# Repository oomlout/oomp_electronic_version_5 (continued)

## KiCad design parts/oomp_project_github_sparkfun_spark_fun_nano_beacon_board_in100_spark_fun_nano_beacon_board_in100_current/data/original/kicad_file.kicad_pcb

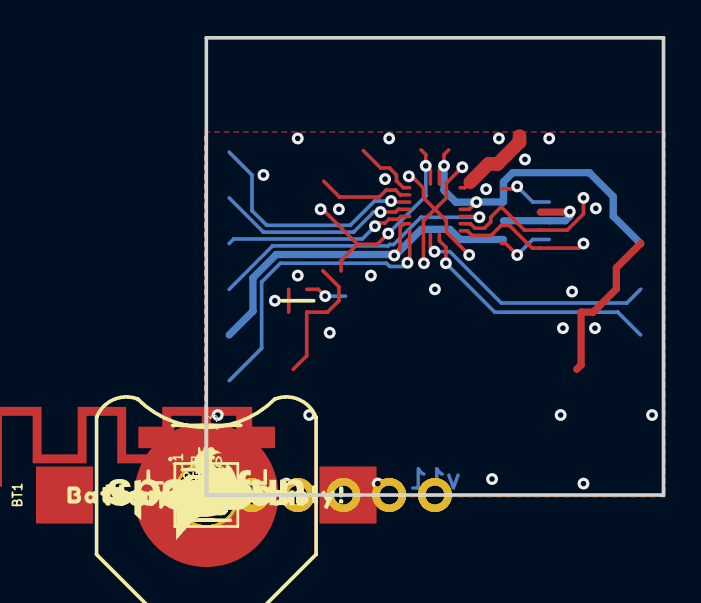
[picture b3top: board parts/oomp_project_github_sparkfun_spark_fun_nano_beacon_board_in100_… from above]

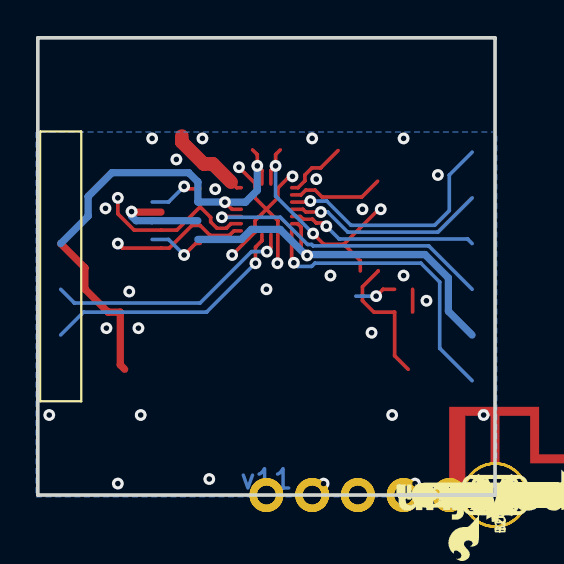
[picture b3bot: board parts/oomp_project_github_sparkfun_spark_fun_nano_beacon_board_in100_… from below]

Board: 2 copper layers, 25.4 x 25.4 mm, 63 parts (24 on the bottom side), 21 nets.

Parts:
BT1: BATTCON_12MM
BUS0: JUMPER-SMT_3_1-NC_TRACE_SILK; SMT-JUMPER_3_1-NC_TRACE_SILK
C1, C3: 0.1uF; 0402-TIGHT
C2: 10uF; 0402-TIGHT
D1: DNP; LED-0402
DEV0: PROD_ID_PASTE_SILK; PRODUCT_IDENT_PASTE_SILK
E1: ANTENNA-GROUNDEDTRACE-15.2MM-MIRROR; TRACE_ANTENNA_2.4GHZ_15.2MM_MIRROR
FD1, FD2, FD3, FD4: FIDUCIAL1X2; FIDUCIAL-1X2
FRAME1: FRAME-LETTER; CREATIVE_COMMONS
H1, H2: STAND-OFF
I2C0: JUMPER-SMT_3_2-NC_TRACE_SILK; SMT-JUMPER_3_2-NC_TRACE_SILK
J1, J2: 1X06_NO_SILK
J3: Vertical Qwiic Connector; JST04_1MM_VERT
LOGO1: OSHW-LOGOS; OSHW-LOGO-S
LOGO2: SFE_LOGO_NAME_FLAME.1_INCH; SFE_LOGO_NAME_FLAME_.1
LOGO3: QWIIC_LOGO_5MM; QWIIC_5MM
PRO0: PROD_ID_PASTE_SILK; PRODUCT_IDENT_PASTE_SILK
PWR0: JUMPER-SMT_2_NC_TRACE_SILK; SMT-JUMPER_2_NC_TRACE_SILK
R1: DNP; 0402-TIGHT
R2: 1k; 0402-TIGHT
R3, R4: 2.2k; 0402-TIGHT
RST0: DNP; TACTILE_SWITCH_SMD_4.6X2.8MM
TP1, TP2, TP3: TEST-POINT3; PAD.03X.03
U1: IN100
U$1, U$29: NANOBEACON0
U$2: #_7#0
U$3: #_6#0
U$4: SFE_LOGO_NAME_.1
U$5, U$31: IN1000
U$6: #_5#0
U$7: #_4#0
U$8: SFE_LOGO_FLAME_.2
U$9: BATTERY_OR_VCC_ONLY##0
U$11: #I2C#0
U$12: #NOTES#0
U$13: #IO7_#0
U$14: #IO6_#0
U$15: #IO5_#0
U$16: #IO4_#0
U$17: #SW0_#0
U$18: #SW1_#0
U$19: #PWR#0
U$20: #SW0#3
U$21: SW00
U$22: SW10
U$23: RST0
U$24: #VCC#0
U$25: #BUS#0
U$26: PWR0
U$28: DEV0
U$30: PRO0
Y1: CRYSTAL-26MHZSMD-3.2X2.5; CRYSTAL-SMD-3.2X2.5MM

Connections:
EN: C3.1, R2.2, RST0.1, RST0.2, TP3.1, U1.18
GND: BT1.GND, C1.2, C2.2, C3.2, E1.GND, J1.6, J3.1, PWR0.1, RST0.3, RST0.4, U1.19, Y1.2, Y1.4
IO4: J2.4, U1.12
IO5: J2.3, U1.5
IO6: J2.2, U1.4
IO7: J2.1, U1.3
unnamed: U1.1, Y1.3
unnamed: U1.2, Y1.1
unnamed: PWR0.2, R1.1
unnamed: E1.ANT, U1.16
unnamed: D1.C, R1.2
unnamed: I2C0.1, R4.2
unnamed: BUS0.2, I2C0.2, J3.2
unnamed: I2C0.3, R3.2
RX/IO0: J1.3, U1.8
SCL/IO2: J3.4, R3.1, TP2.1, U1.10
SDA/IO3: J3.3, R4.1, TP1.1, U1.11
SW0: BUS0.3, J2.5, U1.6
SW1: J2.6, U1.7
TX/IO1: J1.2, U1.9
VCC: BT1.PWR@1, BT1.PWR@2, BUS0.1, C1.1, C2.1, D1.A, J1.4, R2.1, U1.13, U1.17

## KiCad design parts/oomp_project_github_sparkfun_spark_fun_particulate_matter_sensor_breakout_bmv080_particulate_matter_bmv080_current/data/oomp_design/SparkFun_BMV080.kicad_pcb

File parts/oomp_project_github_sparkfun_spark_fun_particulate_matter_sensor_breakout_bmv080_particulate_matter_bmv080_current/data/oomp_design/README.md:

# OOMP KiCad design copy

Open `SparkFun_BMV080.kicad_pro` (or the `.kicad_pcb` / `.kicad_sch`) in KiCad. Local OOMP libraries are under `libraries/`. Original inputs are preserved in [../original/](../original/).

Only verified unchanged installed KiCad defaults were renamed. Modified, custom, unmatched and unavailable items remain unchanged. Soldering variants are never swapped during conversion. Existing pad coordinates, nets and UUIDs are preserved.

See [conversion_report.yaml](conversion_report.yaml) for every conversion and skip. Copy this directory before editing; regeneration refuses to overwrite edited design files.

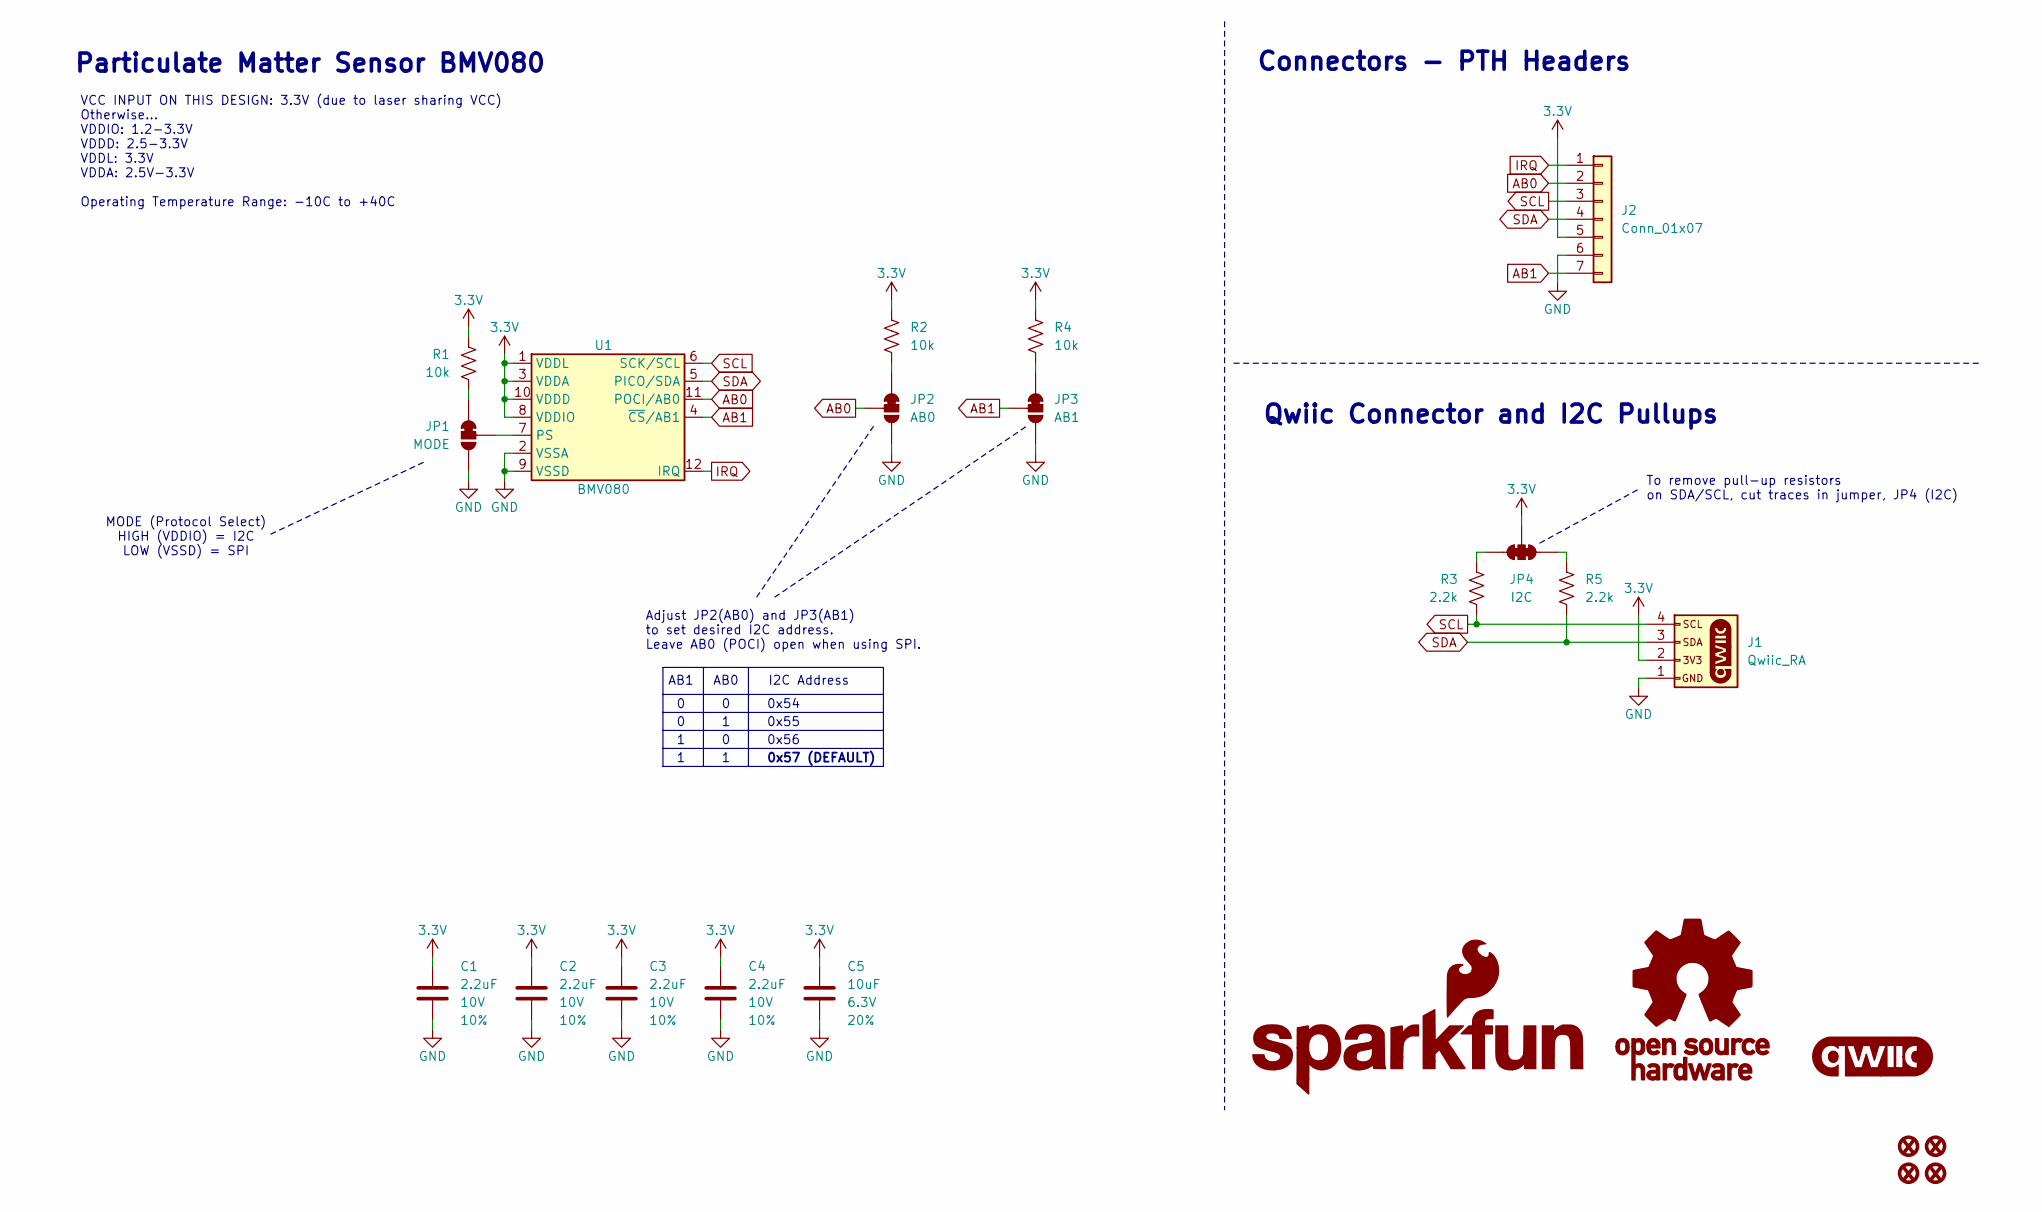
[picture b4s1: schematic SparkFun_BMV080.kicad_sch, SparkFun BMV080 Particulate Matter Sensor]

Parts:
C1, C2, C3, C4: 2.2uF; C_0402_1005Metric; Voltage 10V; Tolerance 10%
C5: 10uF; C_0603_1608Metric; Voltage 6.3V; Tolerance 20%
FID1, FID2, FID3, FID4: Fiducial_0.5mm; Fiducial_0.5mm_Mask1mm
G1: OSHW_Logo; Creative_Commons_License
G2: SparkFun_Logo
G3: qwiic_Logo
J1: Qwiic_RA; JST_SMD_1.0mm-4_RA
J2: Conn_01x07; 1x07
JP1: MODE; Jumper_3_NC-1_Trace_NoSilk
JP2: AB0; Jumper_3_NC-1_Trace_NoSilk
JP3: AB1; Jumper_3_NC-1_Trace_NoSilk
JP4: I2C; Jumper_3_NC-2_Trace_NoSilk
R1, R2, R4: 10k; R_0402_1005Metric
R3, R5: 2.2k; R_0402_1005Metric
U1: BMV080; FPC_0.3mm-13

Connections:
3.3V: C1.1, C2.1, C3.1, C4.1, C5.1, J1.2, J2.5, JP4.2 (C), R1.1, R2.1, R4.1, U1.1 (VDDL), U1.3 (VDDA), U1.8 (VDDIO), U1.10 (VDDD)
AB0: J2.2, JP2.2 (C), U1.11 (POCI/AB0)
AB1: J2.7, JP3.2 (C), U1.4 (~CS/AB1)
GND: C1.2, C2.2, C3.2, C4.2, C5.2, J1.1, J2.6, JP1.3 (B), JP2.3 (B), JP3.3 (B), U1.2 (VSSA), U1.9 (VSSD)
IRQ: J2.1, U1.12 (IRQ)
unnamed: JP1.1 (A), R1.2
unnamed: JP1.2 (C), U1.7 (PS)
unnamed: JP2.1 (A), R2.2
unnamed: JP3.1 (A), R4.2
unnamed: JP4.1 (A), R5.2
unnamed: JP4.3 (B), R3.2
SCL: J1.4, J2.3, R3.1, U1.6 (SCK/SCL)
SDA: J1.3, J2.4, R5.1, U1.5 (PICO/SDA)

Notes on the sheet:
0x54
MODE (Protocol Select) HIGH (VDDIO) = I2C LOW (VSSD) = SPI
AB1
Connectors - PTH Headers
0x57 (DEFAULT)
VCC INPUT ON THIS DESIGN: 3.3V (due to laser sharing VCC) Otherwise... VDDIO: 1.2-3.3V VDDD: 2.5-3.3V VDDL: 3.3V VDDA: 2.5V-3.3V Operating Temperature Range: -10C to +40C
Particulate Matter Sensor BMV080
AB0
0x56
I2C Address
Adjust JP2(AB0) and JP3(AB1) to set desired I2C address. Leave AB0 (POCI) open when using SPI.
0x55
To remove pull-up resistors on SDA/SCL, cut traces in jumper, JP4 (I2C)
Qwiic Connector and I2C Pullups

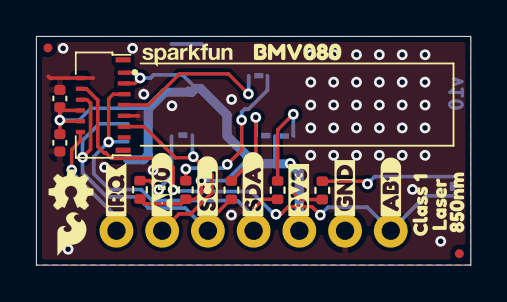
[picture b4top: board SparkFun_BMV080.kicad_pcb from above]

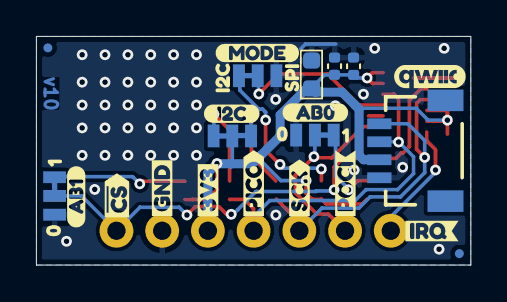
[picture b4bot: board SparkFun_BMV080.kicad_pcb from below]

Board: 2 copper layers, 24.1 x 12.7 mm, 51 parts (27 on the bottom side), 13 nets.

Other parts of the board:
Ref**: Val**; OSHW_Logo_2.5mm
kibuzzard-66BFB450: G***; kibuzzard-66BFB450
kibuzzard-66BFBF9D, kibuzzard-66BFBF9D#2: G***; kibuzzard-66BFBF9D
kibuzzard-66BFBF23: G***; kibuzzard-66BFBF23
kibuzzard-66BFBF70, kibuzzard-66BFBF70#2: G***; kibuzzard-66BFBF70
kibuzzard-66BFC0D2: G***; kibuzzard-66BFC0D2
kibuzzard-66BFC2FE: G***; kibuzzard-66BFC2FE
kibuzzard-66BFC09F: G***; kibuzzard-66BFC09F
kibuzzard-66BFC045: G***; kibuzzard-66BFC045
kibuzzard-66BFC108: G***; kibuzzard-66BFC108
kibuzzard-66BFC288: G***; kibuzzard-66BFC288
kibuzzard-66C3B2A1: G***; kibuzzard-66C3B2A1
kibuzzard-66C3B2DA: G***; kibuzzard-66C3B2DA
kibuzzard-66C3B2FA, kibuzzard-66C3B2FA#2: G***; kibuzzard-66C3B2FA
kibuzzard-66C3B3B1: G***; kibuzzard-66C3B3B1
kibuzzard-66C3B3D3: G***; kibuzzard-66C3B3D3
kibuzzard-66C3B30A, kibuzzard-66C3B30A#2: G***; kibuzzard-66C3B30A
kibuzzard-66C3B31E: G***; kibuzzard-66C3B31E
kibuzzard-66C3B369: G***; kibuzzard-66C3B369
kibuzzard-66C4B81D: G***; kibuzzard-66C4B81D
kibuzzard-66C7A36E: G***; kibuzzard-66C7A36E
kibuzzard-66C77290: G***; kibuzzard-66C77290
kibuzzard-67250BE2: G***; kibuzzard-67250BE2
kibuzzard-67250CD2: G***; kibuzzard-67250CD2
kibuzzard-67250CEE: G***; kibuzzard-67250CEE

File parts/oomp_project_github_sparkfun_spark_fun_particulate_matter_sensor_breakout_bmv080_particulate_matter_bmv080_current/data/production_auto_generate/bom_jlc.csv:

Comment,Designator,Footprint,LCSC Part #
10k,"R1,R2,R4",SparkFun-Resistor:R_0402_1005Metric,C2906861
10uF,C5,SparkFun-Capacitor:C_0603_1608Metric,C19702
2.2k,"R3,R5",SparkFun-Resistor:R_0402_1005Metric,C2906920
2.2uF,"C1,C2,C3,C4",SparkFun-Capacitor:C_0402_1005Metric,C12530
AB0,JP2,SparkFun-Jumper:Jumper_3_NC-1_Trace_NoSilk,
AB1,JP3,SparkFun-Jumper:Jumper_3_NC-1_Trace_NoSilk,
BMV080,U1,SparkFun-Connector:FPC_0.3mm-13,
BMV080_Outline,REF**,SparkFun-Sensor:BMV080_Outline,
Conn_01x07,J2,SparkFun-Connector:1x07,C7501585
I2C,JP4,SparkFun-Jumper:Jumper_3_NC-2_Trace_NoSilk,
MODE,JP1,SparkFun-Jumper:Jumper_3_NC-1_Trace_NoSilk,
Qwiic_RA,J1,SparkFun-Connector:JST_SMD_1.0mm-4_RA,C160404

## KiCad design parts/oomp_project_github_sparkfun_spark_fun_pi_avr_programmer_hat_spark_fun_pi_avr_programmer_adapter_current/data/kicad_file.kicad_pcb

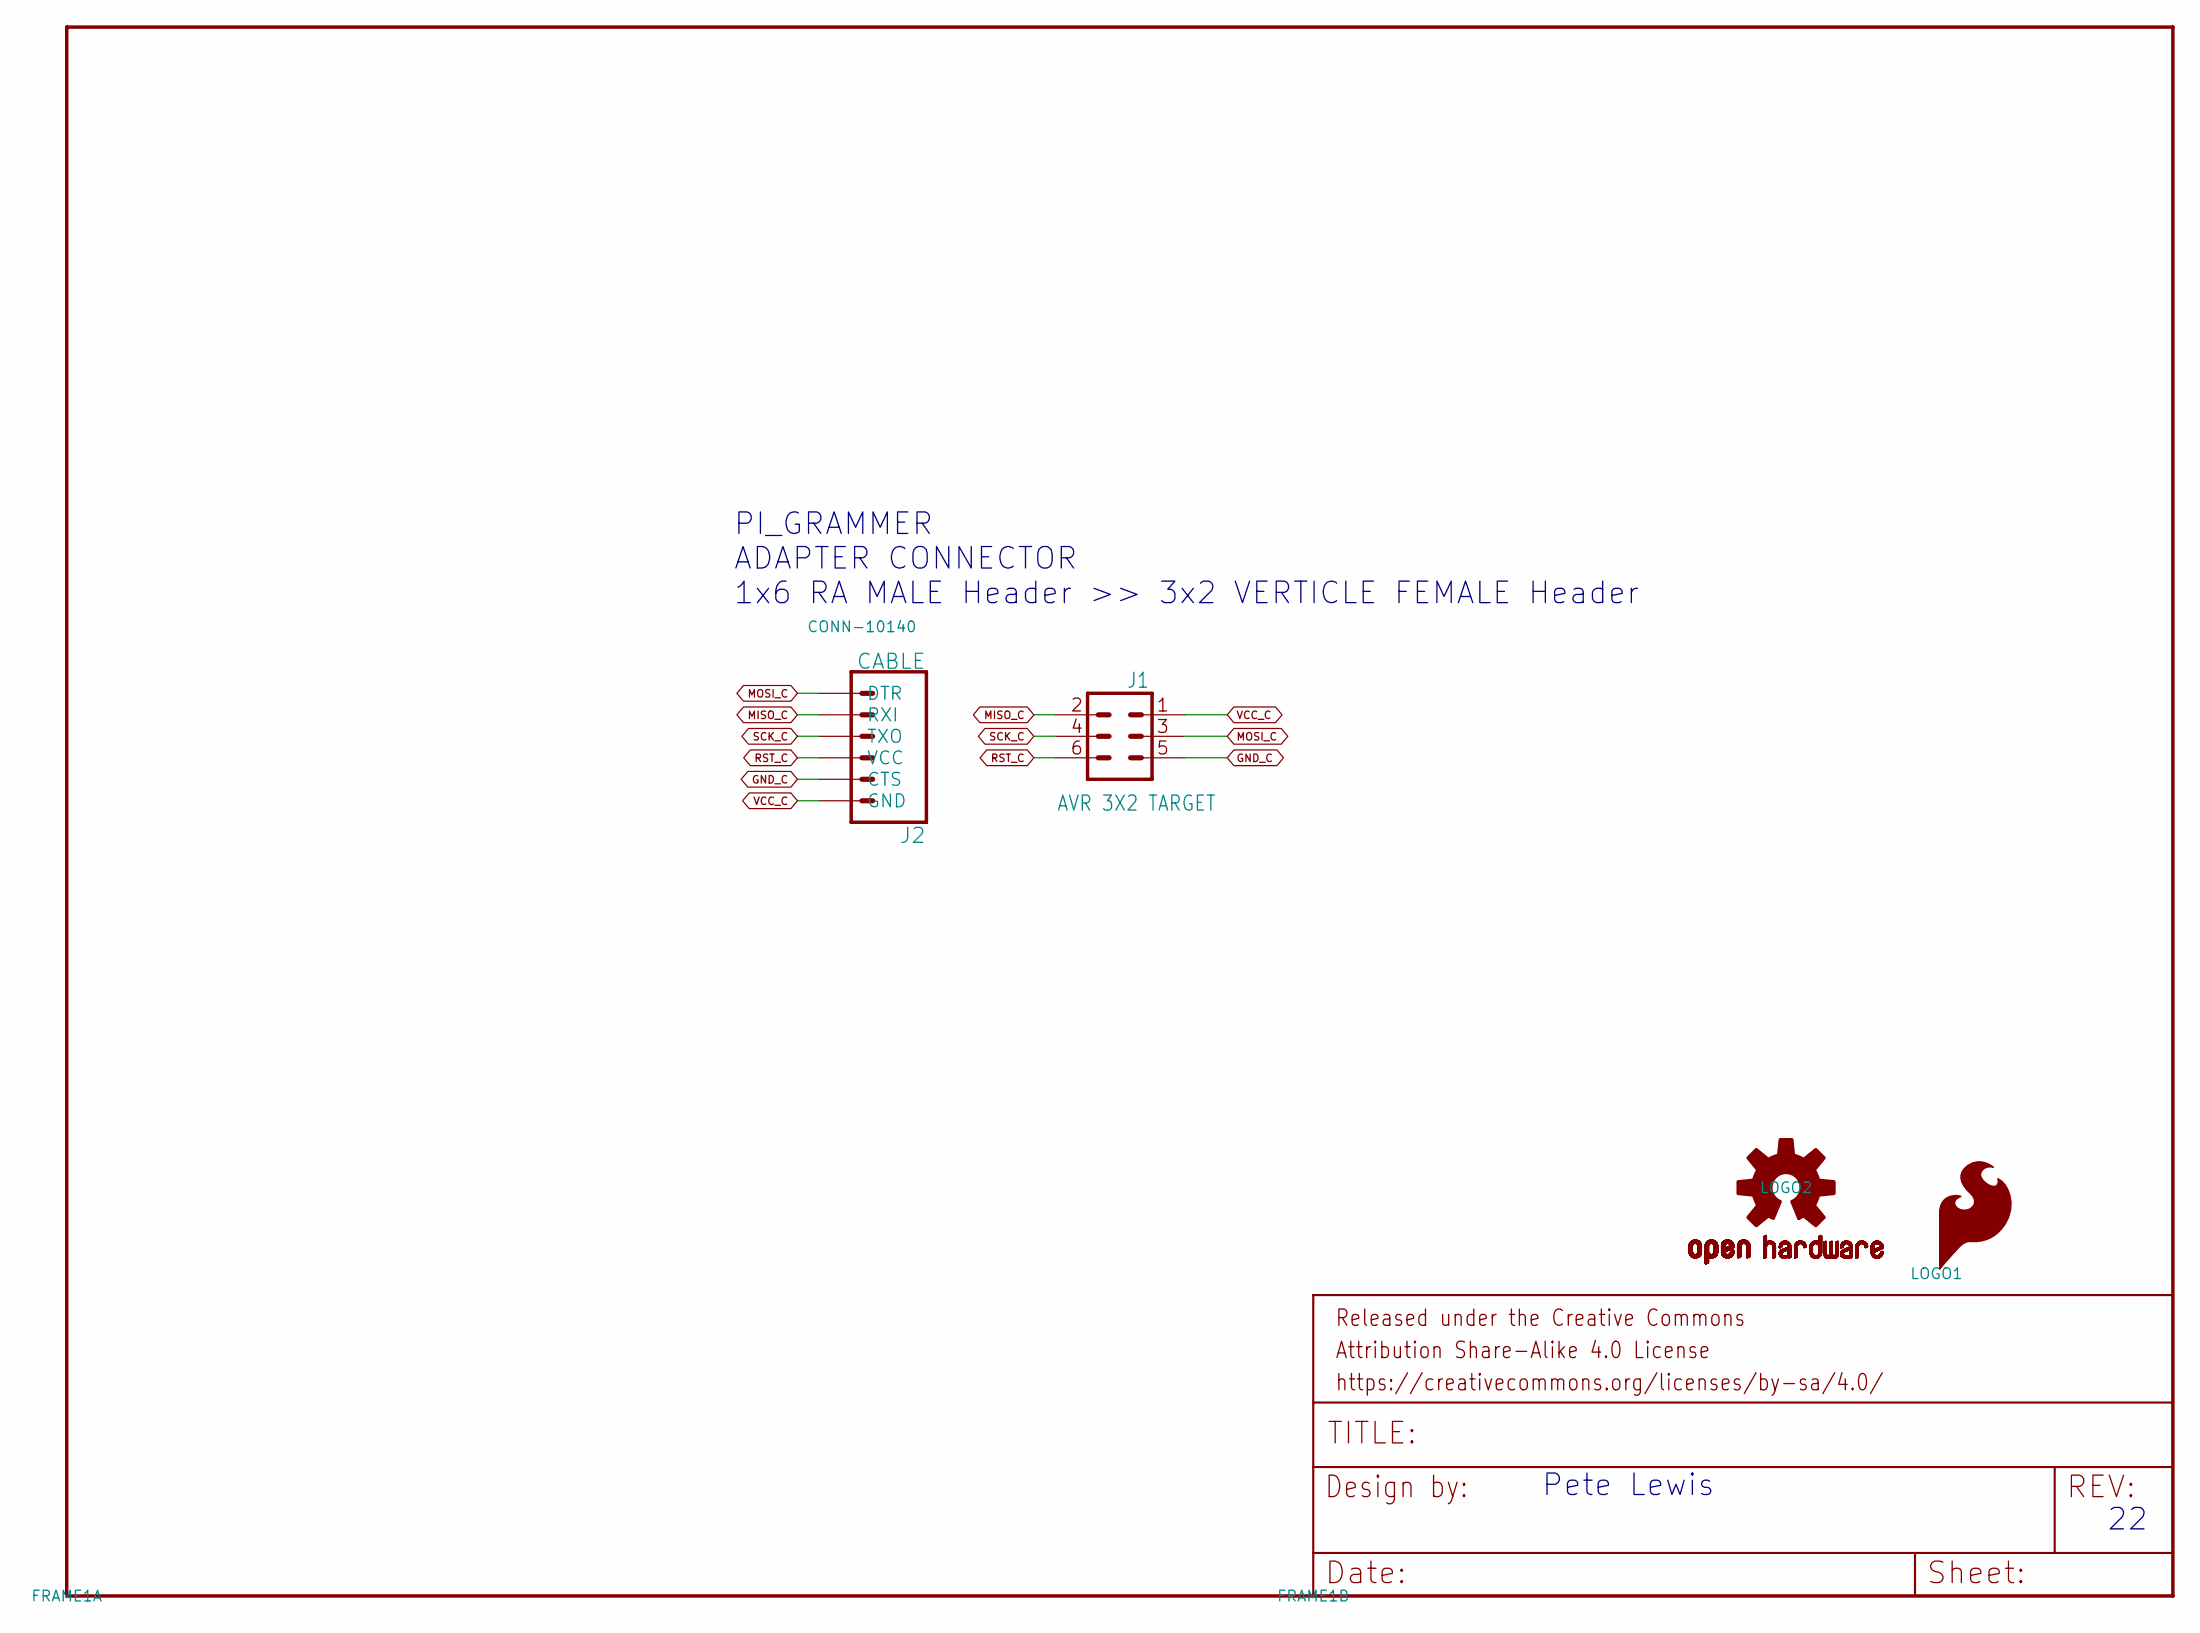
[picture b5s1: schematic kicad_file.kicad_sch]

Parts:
FRAME1: FRAME-LETTER; CREATIVE_COMMONS
J1: AVR 3X2 TARGET; 2X3_SMT_POSTS
J2: CABLE; 1X06-SMD_RA_MALE
LOGO1: SFE_LOGO_FLAME.1_INCH; SFE_LOGO_FLAME_.1
LOGO2: OSHW-LOGOMINI; OSHW-LOGO-MINI

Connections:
GND_C: J1.5, J2.5 (CTS)
MISO_C: J1.2, J2.2 (RXI)
MOSI_C: J1.3, J2.1 (DTR)
RST_C: J1.6, J2.4 (VCC)
SCK_C: J1.4, J2.3 (TXO)
VCC_C: J1.1, J2.6 (GND)

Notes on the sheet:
Pete Lewis
PI_GRAMMER ADAPTER CONNECTOR 1x6 RA MALE Header >> 3x2 VERTICLE FEMALE Header

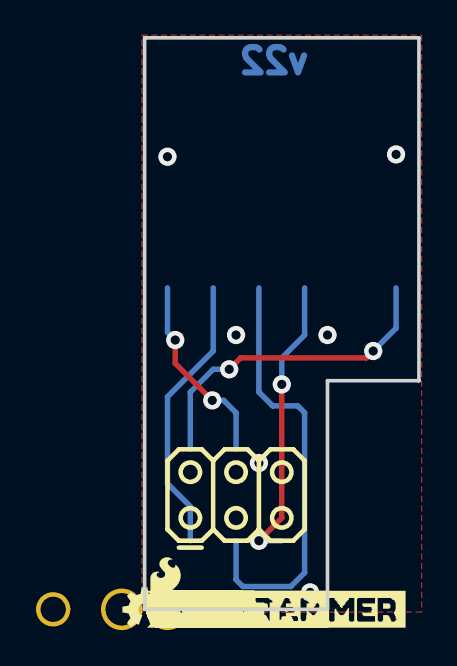
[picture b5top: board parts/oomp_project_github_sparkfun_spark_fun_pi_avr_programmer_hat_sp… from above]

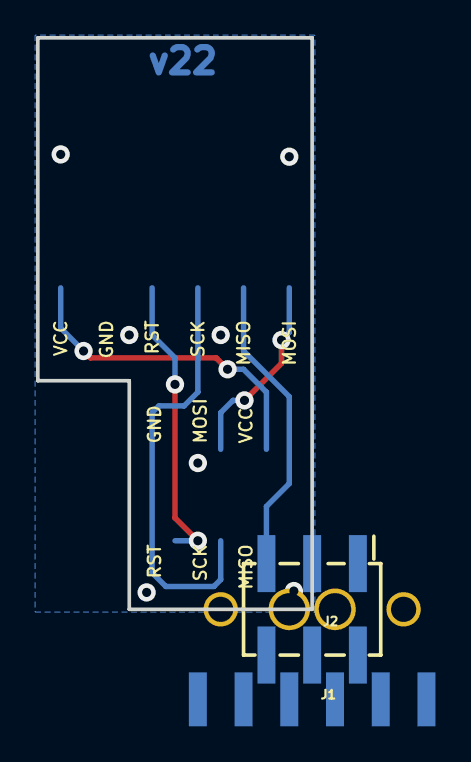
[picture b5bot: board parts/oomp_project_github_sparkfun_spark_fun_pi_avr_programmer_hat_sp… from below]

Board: 2 copper layers, 15.2 x 31.8 mm, 16 parts (2 on the bottom side), 6 nets.

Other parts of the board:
U$1: GND1
U$2: MISO5
U$3: MOSI4
U$4: RST2
U$5: SCK3
U$6: VCC0
U$7: PI0
U$8: AVR1
U$9: PROGRAMMER2
U$10: HAT3
U$11: ADAPTER4

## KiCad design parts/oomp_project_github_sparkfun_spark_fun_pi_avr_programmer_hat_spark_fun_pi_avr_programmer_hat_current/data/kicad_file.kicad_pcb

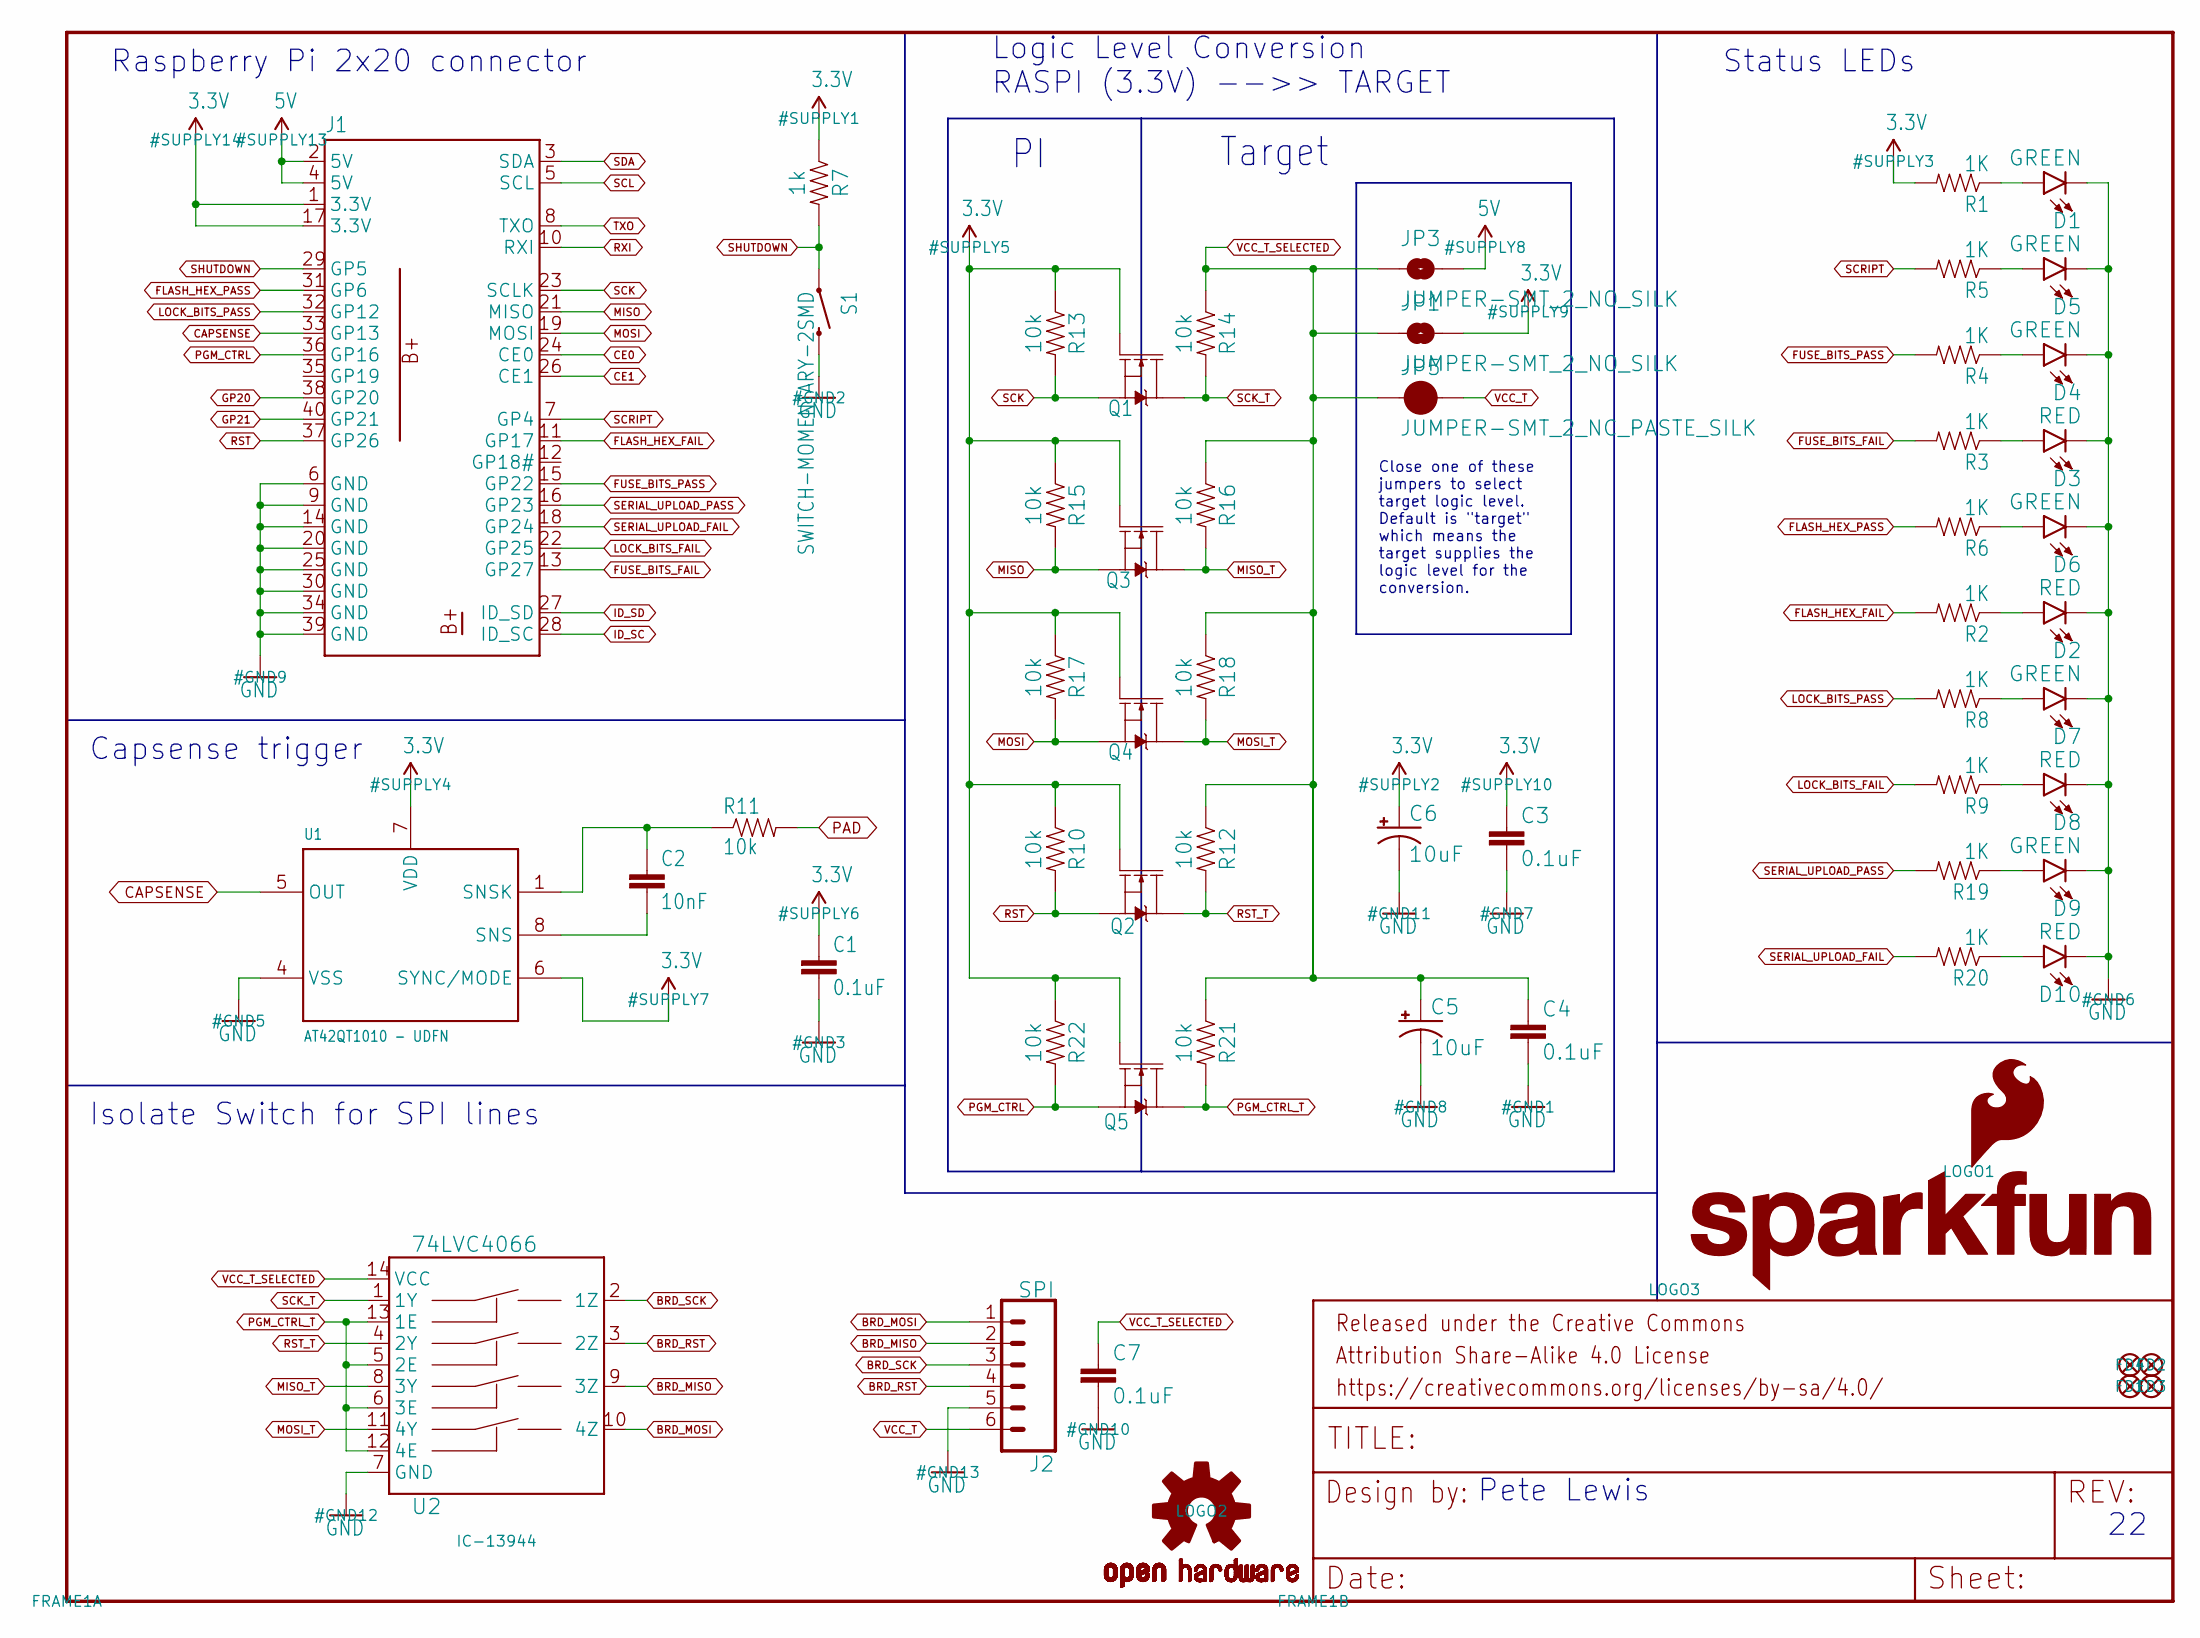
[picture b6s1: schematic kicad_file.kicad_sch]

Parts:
C1: 0.1uF; 0603-CAP
C2: 10nF; 0603-CAP
C3, C4, C7: 0.1uF; 0603
C5, C6: 10uF; EIA3216
D1, D4, D5, D6, D7, D9: GREEN; LED-1206
D2, D3, D8, D10: RED; LED-1206
FD1, FD2, FD3, FD4: FIDUCIALUFIDUCIAL; FIDUCIAL-MICRO
FRAME1: FRAME-LETTER; CREATIVE_COMMONS
J1: RASPBERRYPI-B+-GPIO; 2X20-SHROUDED
J2: SPI; 1X06-SMD_RA_MALE
JP1, JP3: JUMPER-SMT_2_NO_SILK; SMT-JUMPER_2_NO_SILK
JP5: JUMPER-SMT_2_NC_PASTE_SILK; SMT-JUMPER_2_NC_PASTE_SILK
LOGO1: SFE_LOGO_FLAME.2_INCH; SFE_LOGO_FLAME_.2
LOGO2: OSHW-LOGOL; OSHW-LOGO-L
LOGO3: SFE_LOGO_NAME.6_INCH; SFE_LOGO_NAME_.6
Q1, Q2, Q3, Q4, Q5: 220mA/50V/3.5Ω; SOT23-3
R1, R2, R3, R4, R5, R6, R8, R9, R19, R20: 1K; 0603-RES
R7: 1k; 0603
R10, R12, R13, R14, R15, R16, R17, R18, R21, R22: 10k; 0603
R11: 10k; 0603-RES
S1: SWITCH-MOMENTARY-2SMD; TACTILE-SWITCH-SMD
U1: AT42QT1010 - UDFN; UDFN_USON_8_PAD
U2: 74LVC4066; SO14

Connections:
3.3V: C1.1, C3.1, C6.+, J1.1 (3.3V), J1.17 (3.3V), JP1.2, Q1.1 (G), Q2.1 (G), Q3.1 (G), Q4.1 (G), Q5.1 (G), R1.2, R7.1, R10.1, R13.1, R15.1, R17.1, R22.1, U1.6 (SYNC/MODE), U1.7 (VDD)
5V: J1.2 (5V), J1.4 (5V), JP3.2
BRD_MISO: J2.2, U2.9 (3Z)
BRD_MOSI: J2.1, U2.10 (4Z)
BRD_RST: J2.4, U2.3 (2Z)
BRD_SCK: J2.3, U2.2 (1Z)
CAPSENSE: J1.33 (GP13), U1.5 (OUT)
CE0: J1.24 (CE0)
CE1: J1.26 (CE1)
FLASH_HEX_FAIL: J1.11 (GP17), R2.2
FLASH_HEX_PASS: J1.31 (GP6), R6.2
FUSE_BITS_FAIL: J1.13 (GP27), R3.2
FUSE_BITS_PASS: J1.15 (GP22), R4.2
GND: C1.2, C3.2, C4.2, C5.-, C6.-, C7.2, D1.C, D2.C, D3.C, D4.C, D5.C, D6.C, D7.C, D8.C, D9.C, D10.C, J1.6 (GND), J1.9 (GND), J1.14 (GND), J1.20 (GND), J1.25 (GND), J1.30 (GND), J1.34 (GND), J1.39 (GND), J2.5, S1.3 (2), U1.4 (VSS), U2.7 (GND)
GP20: J1.38 (GP20)
GP21: J1.40 (GP21)
ID_SC: J1.28 (ID_SC)
ID_SD: J1.27 (ID_SD)
LOCK_BITS_FAIL: J1.22 (GP25), R9.2
LOCK_BITS_PASS: J1.32 (GP12), R8.2
MISO: J1.21 (MISO), Q3.2 (S), R15.2
MISO_T: Q3.3 (D), R16.2, U2.8 (3Y)
MOSI: J1.19 (MOSI), Q4.2 (S), R17.2
MOSI_T: Q4.3 (D), R18.2, U2.11 (4Y)
unnamed: D6.A, R6.1
unnamed: D1.A, R1.1
unnamed: D2.A, R2.1
unnamed: D3.A, R3.1
unnamed: D7.A, R8.1
unnamed: D4.A, R4.1
unnamed: D5.A, R5.1
unnamed: D8.A, R9.1
unnamed: C2.2, U1.8 (SNS)
unnamed: C2.1, R11.1, U1.1 (SNSK)
unnamed: D9.A, R19.1
unnamed: D10.A, R20.1
PAD: R11.2
PGM_CTRL: J1.36 (GP16), Q5.2 (S), R22.2
PGM_CTRL_T: Q5.3 (D), R21.2, U2.5 (2E), U2.6 (3E), U2.12 (4E), U2.13 (1E)
RST: J1.37 (GP26), Q2.2 (S), R10.2
RST_T: Q2.3 (D), R12.2, U2.4 (2Y)
RXI: J1.10 (RXI)
SCK: J1.23 (SCLK), Q1.2 (S), R13.2
SCK_T: Q1.3 (D), R14.2, U2.1 (1Y)
SCL: J1.5 (SCL)
SCRIPT: J1.7 (GP4), R5.2
SDA: J1.3 (SDA)
SERIAL_UPLOAD_FAIL: J1.18 (GP24), R20.2
SERIAL_UPLOAD_PASS: J1.16 (GP23), R19.2
SHUTDOWN: J1.29 (GP5), R7.2, S1.1
TXO: J1.8 (TXO)
VCC_T: J2.6, JP5.2
VCC_T_SELECTED: C4.1, C5.+, C7.1, JP1.1, JP3.1, JP5.1, R12.1, R14.1, R16.1, R18.1, R21.1, U2.14 (VCC)

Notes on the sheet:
Logic Level Conversion RASPI (3.3V) -->> TARGET
Status LEDs
Capsense trigger
Target
Isolate Switch for SPI lines
Raspberry Pi 2x20 connector
Close one of these jumpers to select target logic level. Default is "target" which means the target supplies the logic level for the conversion.
Pete Lewis

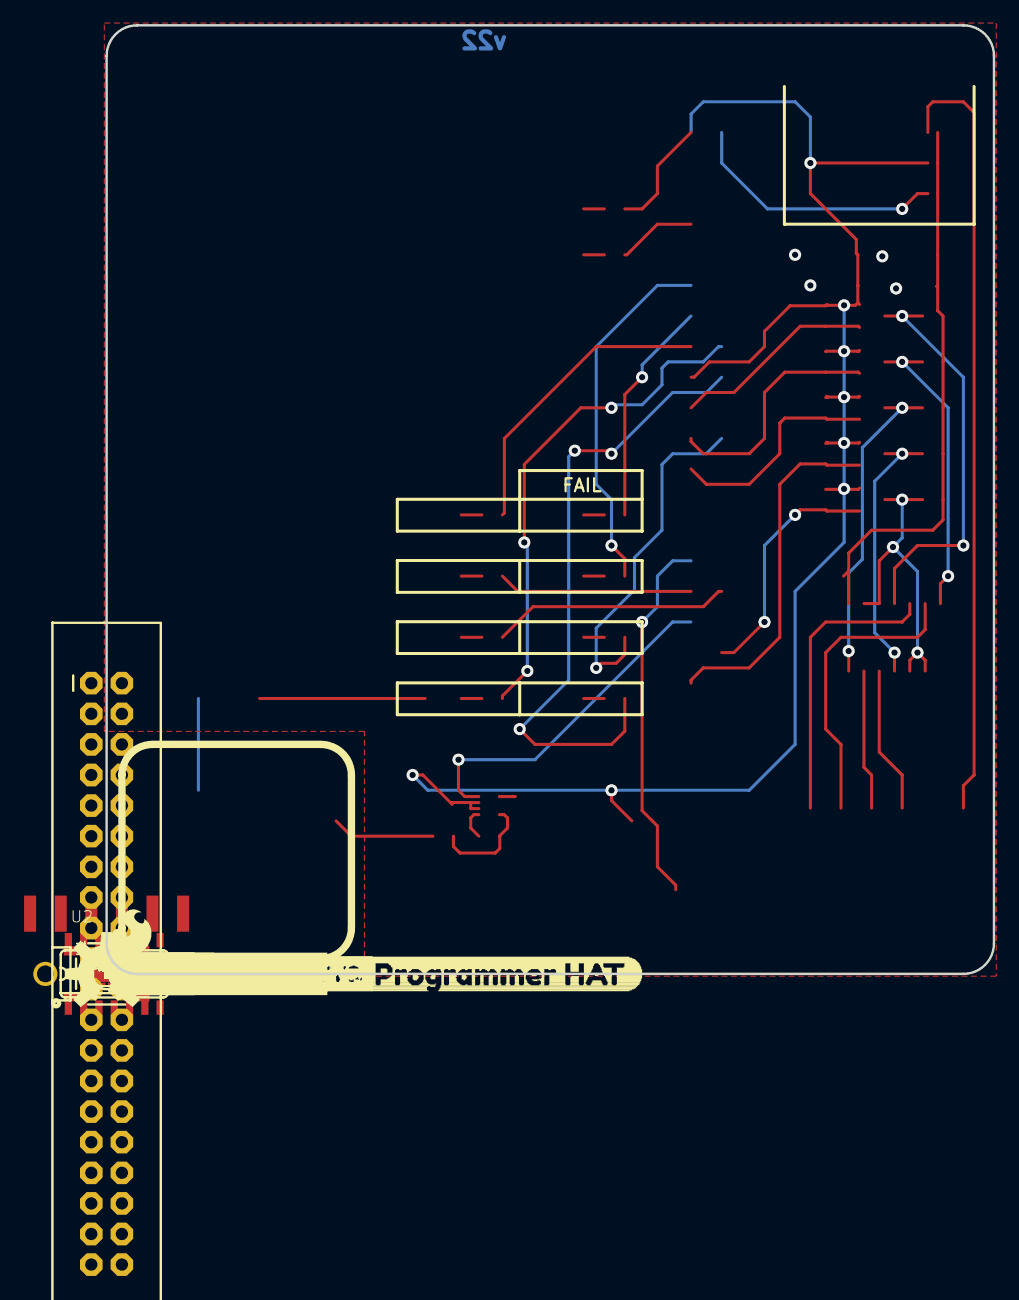
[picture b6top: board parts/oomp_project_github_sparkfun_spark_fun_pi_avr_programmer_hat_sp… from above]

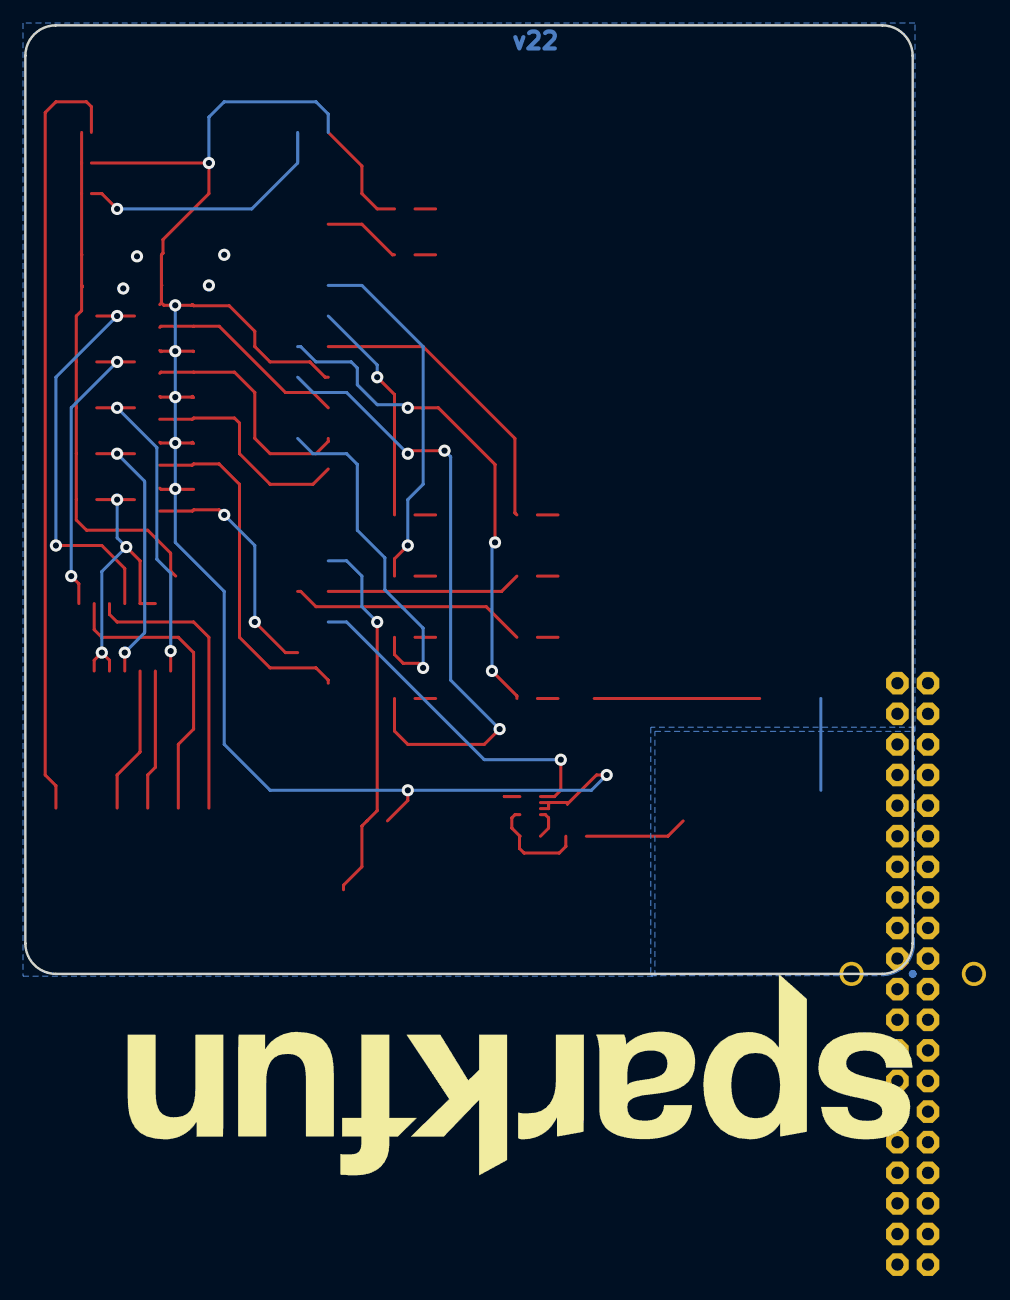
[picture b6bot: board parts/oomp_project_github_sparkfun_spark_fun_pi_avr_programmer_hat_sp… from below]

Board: 2 copper layers, 73.7 x 78.7 mm, 85 parts (3 on the bottom side), 42 nets.

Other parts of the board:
U$1: SPARKFUN_PI_AVR_PROGRAMMER_HAT0
U$2: PROJECT_NAME0
U$3: VERSION_#_DATE_#_ETC#0
U$4: TARGET_LOGIC_SELECT4
U$5: POWER0
U$6: STAT1
U$7: SHUTDOWN2
U$8: RASPI3
U$9: 3#3V_#PI#7
U$10: 5V_#PI#8
U$11: TARGET0
U$12: MISO1
U$13: MOSI0
U$14: SCK2
U$15: RST3
U$16: GND4
U$18: TAP0
U$19: TO1
U$20: PROGRAM2
U$21: VCC0
U$22: SUCCESS0
U$23: FUSE_BITS2
U$24: FLASH_HEX3
U$25: LOCK_BITS4
U$26: SERIAL_UPLOAD5
